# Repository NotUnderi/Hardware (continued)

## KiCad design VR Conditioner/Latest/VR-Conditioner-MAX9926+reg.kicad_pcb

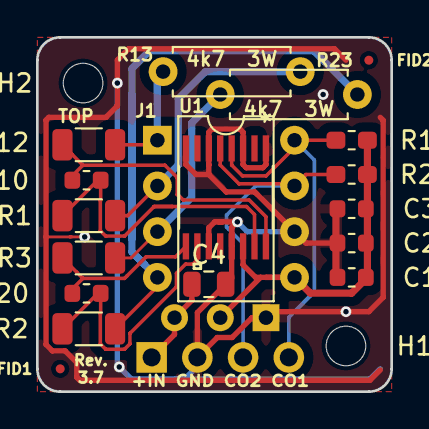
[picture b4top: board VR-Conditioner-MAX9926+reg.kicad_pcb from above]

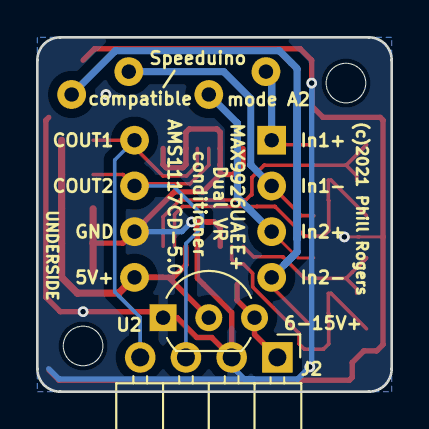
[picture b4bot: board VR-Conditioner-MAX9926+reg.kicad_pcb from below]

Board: 2 copper layers, 19.7 x 19.7 mm, 22 parts (2 on the bottom side), 13 nets.

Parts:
C1: 10n; C_0603_1608Metric
C2: 100n; C_0603_1608Metric
C3: 1u; C_0603_1608Metric
C4: 10u; C_0805_2012Metric
C10, C20: 1n; C_0603_1608Metric
FID1, FID2: Fiducial; Fiducial_0.5mm_Mask1mm
H1, H2: MountingHole; MountingHole_2.2mm_M2
J1: 8-pin header; DIP-8_W7.62mm
J2: Edge; PinHeader_1x04_P2.54mm_Horizontal
R1, R2, R3, R12: 10k; R_1206_3216Metric
R10, R20: 1k; R_0603_1608Metric_Pad1.05x0.95mm_HandSolder
R13, R23: 4.7k; R_Axial_DIN0207_L6.3mm_D2.5mm_P7.62mm_Horizontal
U1: MAX9926UAEE+; MAX9926UAEE&plus_
U2: AMS1117CD-5.0; TO-92_Inline_Wide

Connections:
+12V: C4.1, J2.1, U2.3
/COUT1: J1.8, J2.4, R10.2, U1.4
/COUT2: J1.7, J2.3, R20.2, U1.5
GND: C1.2, C2.2, C3.2, C4.2, J1.6, J2.2, U1.1, U1.3, U1.6, U1.8, U1.11, U1.13, U2.1
unnamed: C10.1, R12.1, U1.16
unnamed: C10.2, R1.1, U1.15
unnamed: C20.1, R2.1, U1.10
unnamed: C20.2, R3.1, U1.9
unnamed: J1.1, R12.2, R13.1
unnamed: J1.2, R1.2, R13.2
unnamed: J1.3, R3.2, R23.1
unnamed: J1.4, R2.2, R23.2
VCC: C1.1, C2.1, C3.1, J1.5, R10.1, R20.1, U1.14, U2.2

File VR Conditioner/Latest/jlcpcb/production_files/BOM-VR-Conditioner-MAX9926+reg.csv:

Comment,Designator,Footprint,LCSC,Quantity
100n,C2,C_0603_1608Metric,C14663,1
10k,"R1,R12,R2,R3",R_1206_3216Metric,C17902,4
10n,C1,C_0603_1608Metric,C57112,1
10u,C4,C_0805_2012Metric,C15850,1
1k,"R10,R20",R_0603_1608Metric_Pad1.05x0.95mm_HandSolder,C21190,2
1n,"C10,C20",C_0603_1608Metric,C1588,2
1u,C3,C_0603_1608Metric,C15849,1
MAX9926UAEE+,U1,MAX9926UAEE&plus_,C970723,1
4.7k,R23,R_Axial_DIN0207_L6.3mm_D2.5mm_P7.62mm_Horizontal,,1
4.7k,R13,R_Axial_DIN0207_L6.3mm_D2.5mm_P7.62mm_Horizontal,,1

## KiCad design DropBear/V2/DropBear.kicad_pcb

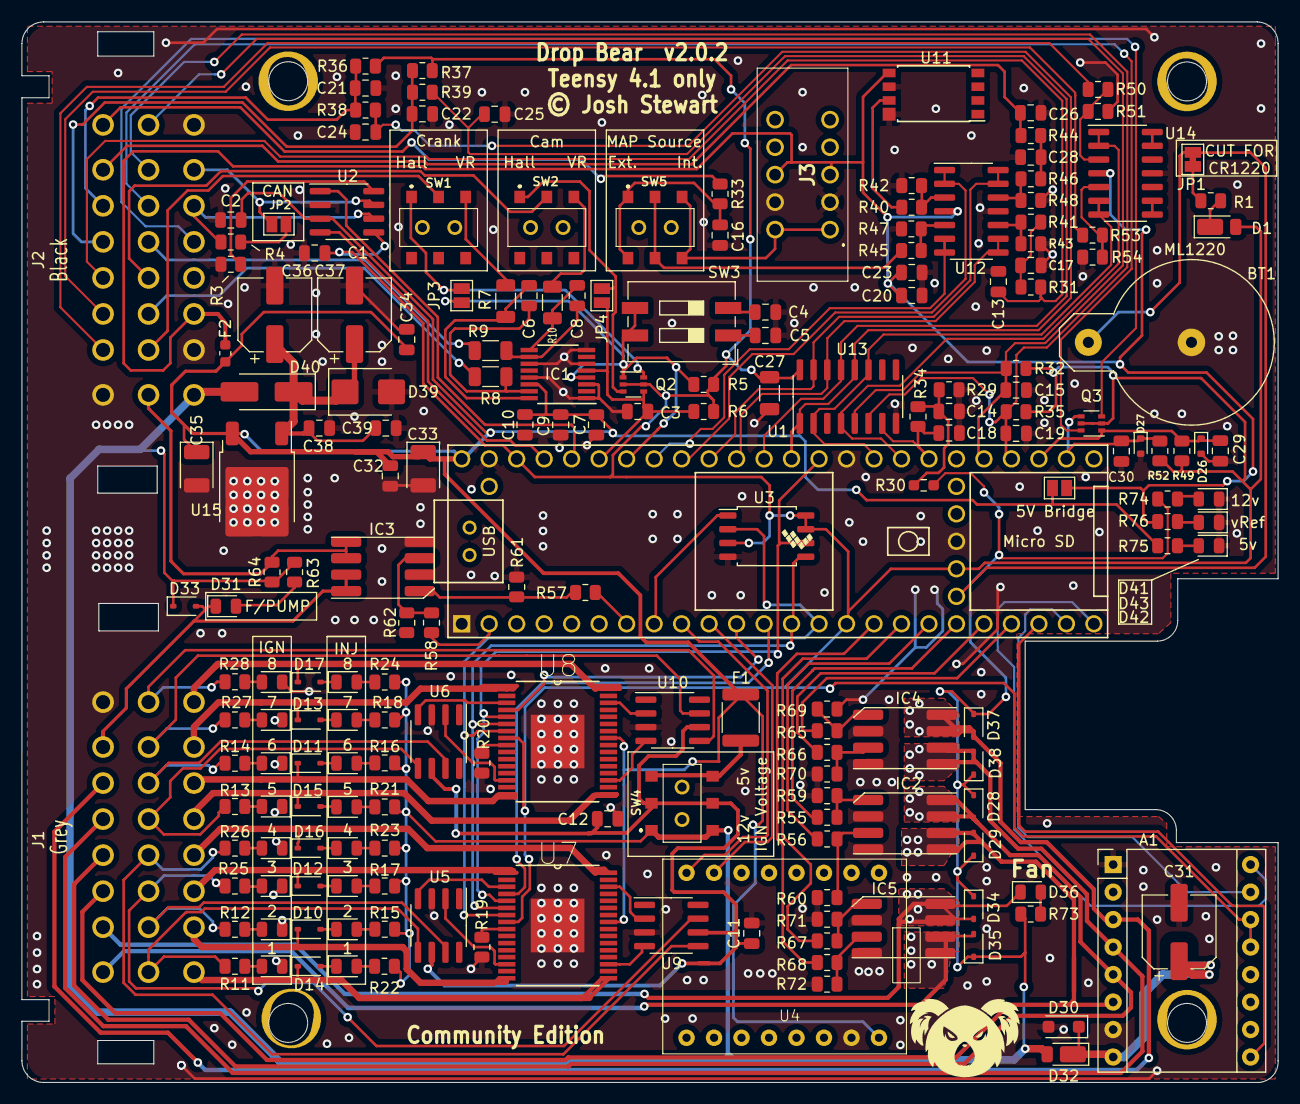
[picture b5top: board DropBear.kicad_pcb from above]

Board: 2 copper layers, 116.1 x 98.0 mm, 196 parts (0 on the bottom side), 161 nets.

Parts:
A1: Pololu_Breakout_DRV8825; Pololu_Breakout-16_15.2x20.3mm
BT1: Battery_Cell; BatteryHolder_Keystone_500
C1, C2, C3, C9, C12, C13, C14, C21, C22, C26, C32, C34, C38: 0.1uF; C_0805_2012Metric
C4, C7, C20, C29, C30: 0.01uF; C_0805_2012Metric
C5, C16: 4700pF; C_0805_2012Metric
C6, C8: 1nF; C_0805_2012Metric
C10, C11, C23: 1uF; C_0805_2012Metric
C15, C19: 270nF; C_0805_2012Metric
C17, C18, C24, C25, C28: 0.22uF; C_0805_2012Metric
C27: 100uF; C_1206_3216Metric
C31: 100uF; CP_Elec_6.3x7.7
C33, C35: 47uF; CP_EIA-3528-21_Kemet-B
C36, C37: 33uF; CP_Elec_6.3x7.7
C39: 0.33uF; C_0805_2012Metric
D1, D32: D_Schottky; D_PowerDI-123
D2, D3, D4, D5, D6, D7, D8, D9, D18, D19, D20, D21, D22, D23, D24, D25, D31, D36, D41, D42, D43: LED; LED_0805_2012Metric
D10, D11, D12, D13, D14, D15, D16, D17, D28, D29, D33, D34, D35, D37, D38: D; D_SOD-323
D26, D27: D_TVS; D_SOD-523
D30: D_TVS; D_SOD-123F
D39: D_TVS; D_SMB
D40: D_Schottky; D_SMA_Handsoldering
F1: Polyfuse; Fuse_1812_4532Metric
F2: Polyfuse; Fuse_0603_1608Metric
IC1: MAX9926UAEE_V+; QSOP-16_3.9x4.9mm_P0.635mm
IC2, IC3, IC4, IC5: ZXMS6006DT8; Diodes_SM8
J1: Delphi_Sicma_24; Delphi_Sicma_24_Grey
J2: Delphi_Sicma_24; Delphi_Sicma_24_Black
J3: EBC05DRXN
JP1: SolderJumper_2_Bridged; SolderJumper-2_P1.3mm_Bridged_Pad1.0x1.5mm
JP2: Jumper_NO_Small; SolderJumper-2_P1.3mm_Open_Pad1.0x1.5mm
JP3, JP4, JP5: Jumper_2_Open; SolderJumper-2_P1.3mm_Open_Pad1.0x1.5mm
Q2, Q3: Q_DUAL_NMOS_S1G1D2S2G2D1; SOT-363_SC-70-6
R1, R31, R33, R34, R38, R39, R44: 470R; R_0805_2012Metric
R3: 0R; R_0805_2012Metric
R4: 120R; R_0805_2012Metric
R5, R6, R11, R12, R13, R14, R15, R16, R17, R18, R21, R22, R23, R24, R25, R26, R27, R28, R35, R49, R52, R55, R56, R57, R58, R63, R65, R66, R67, R68, R73, R75, R76: 1k; R_0805_2012Metric
R7, R8, R9, R10: 10k; R_1206_3216Metric
R19, R20, R64: 10k; R_0805_2012Metric
R29: 604R; R_0805_2012Metric
R30: 3.88k; R_0603_1608Metric_Pad0.98x0.95mm_HandSolder
R32: 2.4k; R_0805_2012Metric
R36, R37, R74: 2.49k; R_0805_2012Metric
R40, R41, R45, R46, R50, R53: 180k; R_0805_2012Metric
R42, R43, R47, R48, R51, R54: 348k; R_0805_2012Metric
R59, R60, R61, R62, R69, R70, R71, R72: 100k; R_0805_2012Metric
SW1, SW2, SW4, SW5: SW_DPDT_x2; AYZ0202AGRLC
SW3: SW_DIP_x02; SW_DIP_SPSTx02_Slide_9.78x7.26mm_W8.61mm_P2.54mm
U1: Teensy4.1; Teensy41
U2: MCP2562-E-SN; SOIC-8_3.9x4.9mm_P1.27mm
U3: W25Q32JVSS; SOIC-8_5.23x5.23mm_P1.27mm
U4: ESP32-C3 SUPERMINI
U5, U6, U9, U10: TC4424A; SOIC-8_3.9x4.9mm_P1.27mm
U7, U8: MC33810; SOIC32-P0.65-33N
U11: KP234
U12, U14: LMV324LIDT; SOIC-14_3.9x8.7mm_P1.27mm
U13: SP720; SOIC-16_3.9x9.9mm_P1.27mm
U15: MC78M05_TO252; TO-252-2

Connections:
12V-PROT: C36.1, C37.1, C38.1, C39.1, D39.1 (K), D40.1 (K), U15.1 (VI)
12V-SW: D28.1 (K), D29.1 (K), D32.2 (A), D33.1 (K), D34.1 (K), D35.1 (K), D37.1 (K), D38.1 (K), D40.2 (A), J2.A1, R15.1, R16.1, R17.1, R18.1, R21.2, R22.2, R23.2, R24.2, R30.2, R63.1, R64.2, R73.1, R74.2, SW4.1 (NC_1), SW4.4 (NC_2)
+3V3: A1.13 (~RST), A1.14 (~SLP), C1.1, C27.2, D1.2 (A), Q2.2 (G), Q2.5 (G), Q3.2 (G), Q3.5 (G), R5.2, R6.1, R32.1, R35.2, R36.2, R37.2, R49.2, R52.2, U1.15 (3V3), U1.46 (3V3), U1.51 (3V3), U2.5 (Vio), U3.3 (IO2), U3.7 (IO3), U3.8 (VCC), U7.8 (VDD), U8.8 (VDD), U13.16 (V+)
+5V: C2.2, C7.1, C9.1, C10.1, C32.1, C33.1, C34.1, C35.1, F1.2, F2.1, IC1.14 (VCC), JP5.1 (A), R75.1, U1.48 (VIN), U2.3 (VDD), U4.1 (5V), U7.25 (VPWR), U8.25 (VPWR), U15.3 (VO)
ADC-Clamp-1: C24.1, R38.1, U1.36 (14_A0_TX3_SPDIF_OUT), U13.1 (I1), U13.12 (I11)
ADC-Clamp-4: U1.32 (40_A16), U13.4 (I4), U14.1, U14.2 (-)
ADC-Clamp-5: C15.1, J2.B8, R32.2, U1.29 (37_CS), U13.5 (I5)
ADC-Clamp-6: C19.1, J2.B7, R35.1, U1.28 (36_CS), U13.6 (I6)
ADC-Clamp-7: C18.1, R34.1, U1.31 (39_MISO1_OUT1A), U13.7 (I7)
ADC-Clamp-10: U1.33 (41_A17), U13.2 (I2), U13.11 (I10), U14.6 (-), U14.7
ADC-Clamp-12: C25.1, R39.1, U1.37 (15_A1_RX3_SPDIF_IN), U13.13 (I12)
ADC-Clamp-13: U1.38 (16_A2_RX4_SCL1), U12.8, U12.9 (-), U13.14 (I13)
ADC-Clamp-14: U1.39 (17_A3_TX4_SDA1), U12.13 (-), U12.14, U13.15 (I14)
BARO-5V: R40.2, U11.7 (Vout)
BOOST-OUT: D35.2 (A), IC5.5 (DRAIN_2_1), IC5.6 (DRAIN_2_2), J1.C1
CAM-IN+: J2.B4, SW2.2 (B)
CAM-IN-: J2.B5, R9.1
CAN_H: J2.A7, JP2.1, U2.7 (CANH)
CAN_L: J2.A6, R4.1, U2.6 (CANL)
CLT_Sensor: C22.1, J2.C5, R37.1, R39.2
CRANK-IN+: J2.B2, SW1.2 (B)
CRANK-IN-: J2.B3, R8.1
FAN-OUT: D34.2 (A), D36.1 (K), IC5.7 (DRAIN_1_1), IC5.8 (DRAIN_1_2), J1.C2
FUELPUMP-OUT: D31.1 (K), D33.2 (A), IC3.7 (DRAIN_1_1), IC3.8 (DRAIN_1_2), J1.C7
GND: A1.1 (GND), A1.7 (GND), BT1.2 (-), C1.2, C2.1, C3.1, C4.1, C5.2, C7.2, C9.2, C10.2, C11.2, C12.2, C13.2, C14.2, C15.2, C16.1, C17.2, C18.2, C19.2, C20.1, C21.2, C22.2, C23.1, C24.2, C25.2, C26.2, C27.1, C28.2, C29.1, C30.1, C31.2, C32.2, C33.2, C34.2, C35.2, C36.2, C37.2, C38.2, C39.2, D2.1 (K), D3.1 (K), D4.1 (K), D5.1 (K), D22.1 (K), D23.1 (K), D24.1 (K), D25.1 (K), D26.2 (A2), D27.2 (A2), D30.2 (A), D39.2 (A), D41.1 (K), D42.1 (K), D43.1 (K), IC1.1 (IN_THRS1), IC1.3 (BIAS1), IC1.6 (BIAS2), IC1.8 (INT_THRS2), IC1.11 (GND), IC1.13 (ZERO_EN), IC2.2 (SOURCE_1), IC2.4 (SOURCE_2), IC3.2 (SOURCE_1), IC3.4 (SOURCE_2), IC4.2 (SOURCE_1), IC4.4 (SOURCE_2), IC5.2 (SOURCE_1), IC5.4 (SOURCE_2), J1.C8, J2.A2, J2.A8, J2.C1, J3.A2, J3.B2, R3.1, R19.2, R20.2, R29.1, R42.1, R43.1, R47.1, R48.1, R51.1, R54.1, R59.2, R60.1, R61.2, R62.1, R69.2, R70.1, R71.2, R72.1, U1.1 (GND), U1.34 (GND), U1.47 (GND), U1.52 (GND), U2.2 (VSS), U3.4 (GND), U4.3 (GND), U5.3 (GND), U6.3 (GND), U7.33 (GND), U8.33 (GND), U9.3 (GND), U10.3 (GND), U11.6 (GND), U11.8 (GND), U12.11 (V-), U13.8 (GND), U14.11 (V-), U15.2 (GND)
IAT_Sensor: C21.1, J2.C6, R36.1, R38.2
IDLE-OUT: A1.5 (B1), D28.2 (A), IC2.7 (DRAIN_1_1), IC2.8 (DRAIN_1_2), J1.C4
IGN1: J1.B1, R11.2, U5.5 (OUT_B)
IGN2: J1.B2, R12.2, U5.7 (OUT_A)
IGN3: J1.B3, R25.2, U9.7 (OUT_A)
IGN4: J1.B4, R26.2, U9.5 (OUT_B)
IGN5: J1.B5, R13.2, U6.5 (OUT_B)
IGN6: J1.B6, R14.2, U6.7 (OUT_A)
IGN7: J1.B7, R27.2, U10.7 (OUT_A)
IGN8: J1.B8, R28.2, U10.5 (OUT_B)
IGN_V+: C11.1, C12.1, SW4.2 (C_1), SW4.5 (C_2), U5.6 (VDD), U6.6 (VDD), U9.6 (VDD), U10.6 (VDD)
INJ1: D14.1 (K), J1.A1, U7.17 (OUT3)
INJ2: D10.1 (K), J1.A2, U7.16 (OUT1)
INJ3: D12.1 (K), J1.A3, U7.1 (OUT0)
INJ4: D16.1 (K), J1.A4, U7.32 (OUT2)
INJ5: D15.1 (K), J1.A5, U8.17 (OUT3)
INJ6: D11.1 (K), J1.A6, U8.16 (OUT1)
INJ7: D13.1 (K), J1.A7, U8.1 (OUT0)
INJ8: D17.1 (K), J1.A8, U8.32 (OUT2)
MAP-5V: R45.2, SW5.2 (C_1), SW5.5 (C_2)
MAP_External: J2.C8, R33.1
MC33810_1-CS: U1.12 (10_CS_MQSR), U7.4 (CS)
MC33810_2-CS: U1.11 (9_OUT1C), U8.4 (CS)
MCU-A4: U1.40 (18_A4_SDA), U12.1, U12.2 (-)
MCU-A5: U1.41 (19_A5_SCL), U12.6 (-), U12.7
MCU-A6: IC1.4 (COUT1), JP3.2 (B), Q2.1 (S), R5.1, SW3.3, SW3.4, U1.42 (20_A6_TX5_LRCLK1)
MCU-A7: C3.2, IC1.5 (COUT2), JP4.1 (A), Q2.4 (S), R6.2, U1.43 (21_A7_RX5_BCLK1)
MCU-A8: U1.44 (22_A8_CTX1), U2.1 (TXD)
MCU-A9: U1.45 (23_A9_CRX1_MCLK1), U2.4 (RXD)
MCU-D0: R58.2, U1.2 (0_RX1_CRX2_CS1)
MCU-D5: R57.2, U1.7 (5_IN2)
MCU-D6: U1.8 (6_OUT1D), U3.1 (~CS)
MCU-D7: U1.9 (7_RX2_OUT1A), U4.16 (21/TX)
MCU-D8: U1.10 (8_TX2_IN1), U4.14 (20/RX)
MCU-D24: R68.2, U1.16 (24_A10_TX6_SCL2)
MCU-D25: R67.2, U1.17 (25_A11_RX6_SDA2)
MCU-D26: R56.2, U1.18 (26_A12_MOSI1)
MCU-D27: R55.2, U1.19 (27_A13_SCK1)
MCU-D28: R66.2, U1.20 (28_RX7)
MCU-D29: R65.2, U1.21 (29_TX7)
MCU-D30: A1.9 (~EN), U1.22 (30_CRX3)
MCU-D31: A1.15 (STEP), U1.23 (31_CTX3)
MCU-D32: A1.16 (DIR), U1.24 (32_OUT1B)
MCU-D34: C30.2, D27.1 (A1), Q3.4 (S), R52.1, U1.26 (34_RX8)
MCU-D35: C29.2, D26.1 (A1), Q3.1 (S), R49.1, U1.27 (35_TX8)
MISO: U1.14 (12_MISO_MQSL), U3.2 (DO(IO1)), U7.7 (SO), U8.7 (SO)
MOSI: U1.13 (11_MOSI_CTX1), U3.5 (DI(IO0)), U7.6 (SI), U8.6 (SI)
unnamed: A1.8 (VMOT), C31.1, D30.1 (K), D32.1 (K)
unnamed: C4.2, SW3.2
unnamed: C5.1, SW3.1
unnamed: C14.1, R29.2, R30.1, R34.2
unnamed: D1.1 (K), R1.2
unnamed: D2.2 (A), R11.1
unnamed: D3.2 (A), R12.1
unnamed: D4.2 (A), R13.1
unnamed: D5.2 (A), R14.1
unnamed: D6.2 (A), R15.2
unnamed: D7.2 (A), R16.2
unnamed: D8.2 (A), R17.2
unnamed: D9.2 (A), R18.2
unnamed: D6.1 (K), D10.2 (A)
unnamed: D7.1 (K), D11.2 (A)
unnamed: D8.1 (K), D12.2 (A)
unnamed: D9.1 (K), D13.2 (A)
unnamed: D14.2 (A), D19.1 (K)
unnamed: D15.2 (A), D18.1 (K)
unnamed: D16.2 (A), D20.1 (K)
unnamed: D17.2 (A), D21.1 (K)
unnamed: D18.2 (A), R21.1
unnamed: D19.2 (A), R22.1
unnamed: D20.2 (A), R23.1
unnamed: D21.2 (A), R24.1
unnamed: D22.2 (A), R25.1
unnamed: D23.2 (A), R26.1
unnamed: D24.2 (A), R27.1
unnamed: D25.2 (A), R28.1
unnamed: D31.2 (A), R63.2
unnamed: D36.2 (A), R73.2
unnamed: D41.2 (A), R74.1
unnamed: D42.2 (A), R75.2
unnamed: D43.2 (A), R76.2
unnamed: C6.1, IC1.16 (IN1+), R7.2
unnamed: C6.2, IC1.15 (IN1-), R8.2
unnamed: C8.2, IC1.9 (IN2+), R10.2
unnamed: C8.1, IC1.10 (IN2-), R9.2
unnamed: IC2.1 (INPUT_1), R55.1, R59.1
unnamed: IC2.3 (INPUT_2), R56.1, R60.2
unnamed: IC3.1 (INPUT_1), R57.1, R61.1
unnamed: IC3.3 (INPUT_2), R58.1, R62.2
unnamed: IC4.1 (INPUT_1), R65.1, R69.1
unnamed: IC4.3 (INPUT_2), R66.1, R70.2
unnamed: IC5.1 (INPUT_1), R67.1, R71.1
unnamed: IC5.3 (INPUT_2), R68.1, R72.2
unnamed: JP1.1 (A), R1.1
unnamed: JP2.2, R4.2
unnamed: JP3.1 (A), Q2.6 (D), SW1.1 (A)
unnamed: JP4.2 (B), Q2.3 (D), SW2.1 (A)
unnamed: F1.1, SW4.3 (NO_1), SW4.6 (NO_2)
unnamed: C16.2, R33.2, SW5.1 (NC_1), SW5.4 (NC_2)
unnamed: J3.A1, J3.B1, SW5.3 (NO_1), SW5.6 (NO_2)
unnamed: R3.2, U2.8 (STBY)
unnamed: U5.2 (IN_A), U7.14 (GD1)
unnamed: U5.4 (IN_B), U7.3 (GD0)
unnamed: U6.2 (IN_A), U8.14 (GD1)
unnamed: U6.4 (IN_B), U8.3 (GD0)
unnamed: U7.30 (GD2), U9.2 (IN_A)
unnamed: U7.19 (GD3), U9.4 (IN_B)
unnamed: U8.30 (GD2), U10.2 (IN_A)
unnamed: U8.19 (GD3), U10.4 (IN_B)
unnamed: R40.1, R42.2, U12.3 (+)
unnamed: R45.1, R47.2, U12.5 (+)
unnamed: R41.1, R43.2, U12.10 (+)
unnamed: R46.1, R48.2, U12.12 (+)
unnamed: R50.1, R51.2, U14.3 (+)
unnamed: R53.1, R54.2, U14.5 (+)
unnamed: U14.8, U14.9 (-)
unnamed: U14.13 (-), U14.14
O2-5V: C17.1, R31.1, R41.2
O2_Sensor: C13.1, J2.C4, R31.2
OUTEN_1: R19.1, U7.9 (OUTEN)
OUTEN_2: R20.1, U8.9 (OUTEN)
SCLK: U1.35 (13_SCK_LED), U3.6 (CLK), U7.5 (SCLK), U8.5 (SCLK)
SPARE1-Digital: J2.B6, Q3.6 (D)
SPARE1-OUT: A1.3 (A2), D37.2 (A), IC4.7 (DRAIN_1_1), IC4.8 (DRAIN_1_2), J1.C6
SPARE1_Sensor: J2.C2, R50.2
SPARE2-Digital: J2.A5, Q3.3 (D)
SPARE2-OUT: A1.6 (B2), D29.2 (A), IC2.5 (DRAIN_2_1), IC2.6 (DRAIN_2_2), J1.C3
SPARE2_Sensor: J2.C3, R53.2
STEPPER-A1: A1.4 (A1), D38.2 (A), IC4.5 (DRAIN_2_1), IC4.6 (DRAIN_2_2), J1.C5
TACHO-OUT: IC3.5 (DRAIN_2_1), IC3.6 (DRAIN_2_2), J2.B1, R64.1
TPS-5V: C28.1, R44.1, R46.2
TPS_Sensor: C26.1, J2.C7, R44.2
VBat: BT1.1 (+), JP1.2 (B), U1.50 (VBAT)
VDDA: C20.2, C23.2, F2.2, J2.A3, J3.A3, J3.B3, JP5.2 (B), R76.1, U11.5 (Vcc), U12.4 (V+), U14.4 (V+)
VR1-IN+: R7.1, SW1.3 (C)
VR2-IN+: R10.1, SW2.3 (C)

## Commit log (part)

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2026-04-04 Dropbear v2.0.2 minor update
2026-04-04 Dropbear v2.0.2 BOM
2026-06-16 Created NCV1124 based VR conditioner for Speeduino
2026-06-28 Created an interface board for a 3rd gen 4E-FE
2026-06-29 Add prod files for NVC1124
2026-06-29 Add prod files for MAX9926 VR cond
2026-06-29 Changed to THT resistors due to wattage requirements as per ncv1124 datasheet. Added prod files
2026-06-29 Small brainfart with the layout. Updated pcb and gerbers
